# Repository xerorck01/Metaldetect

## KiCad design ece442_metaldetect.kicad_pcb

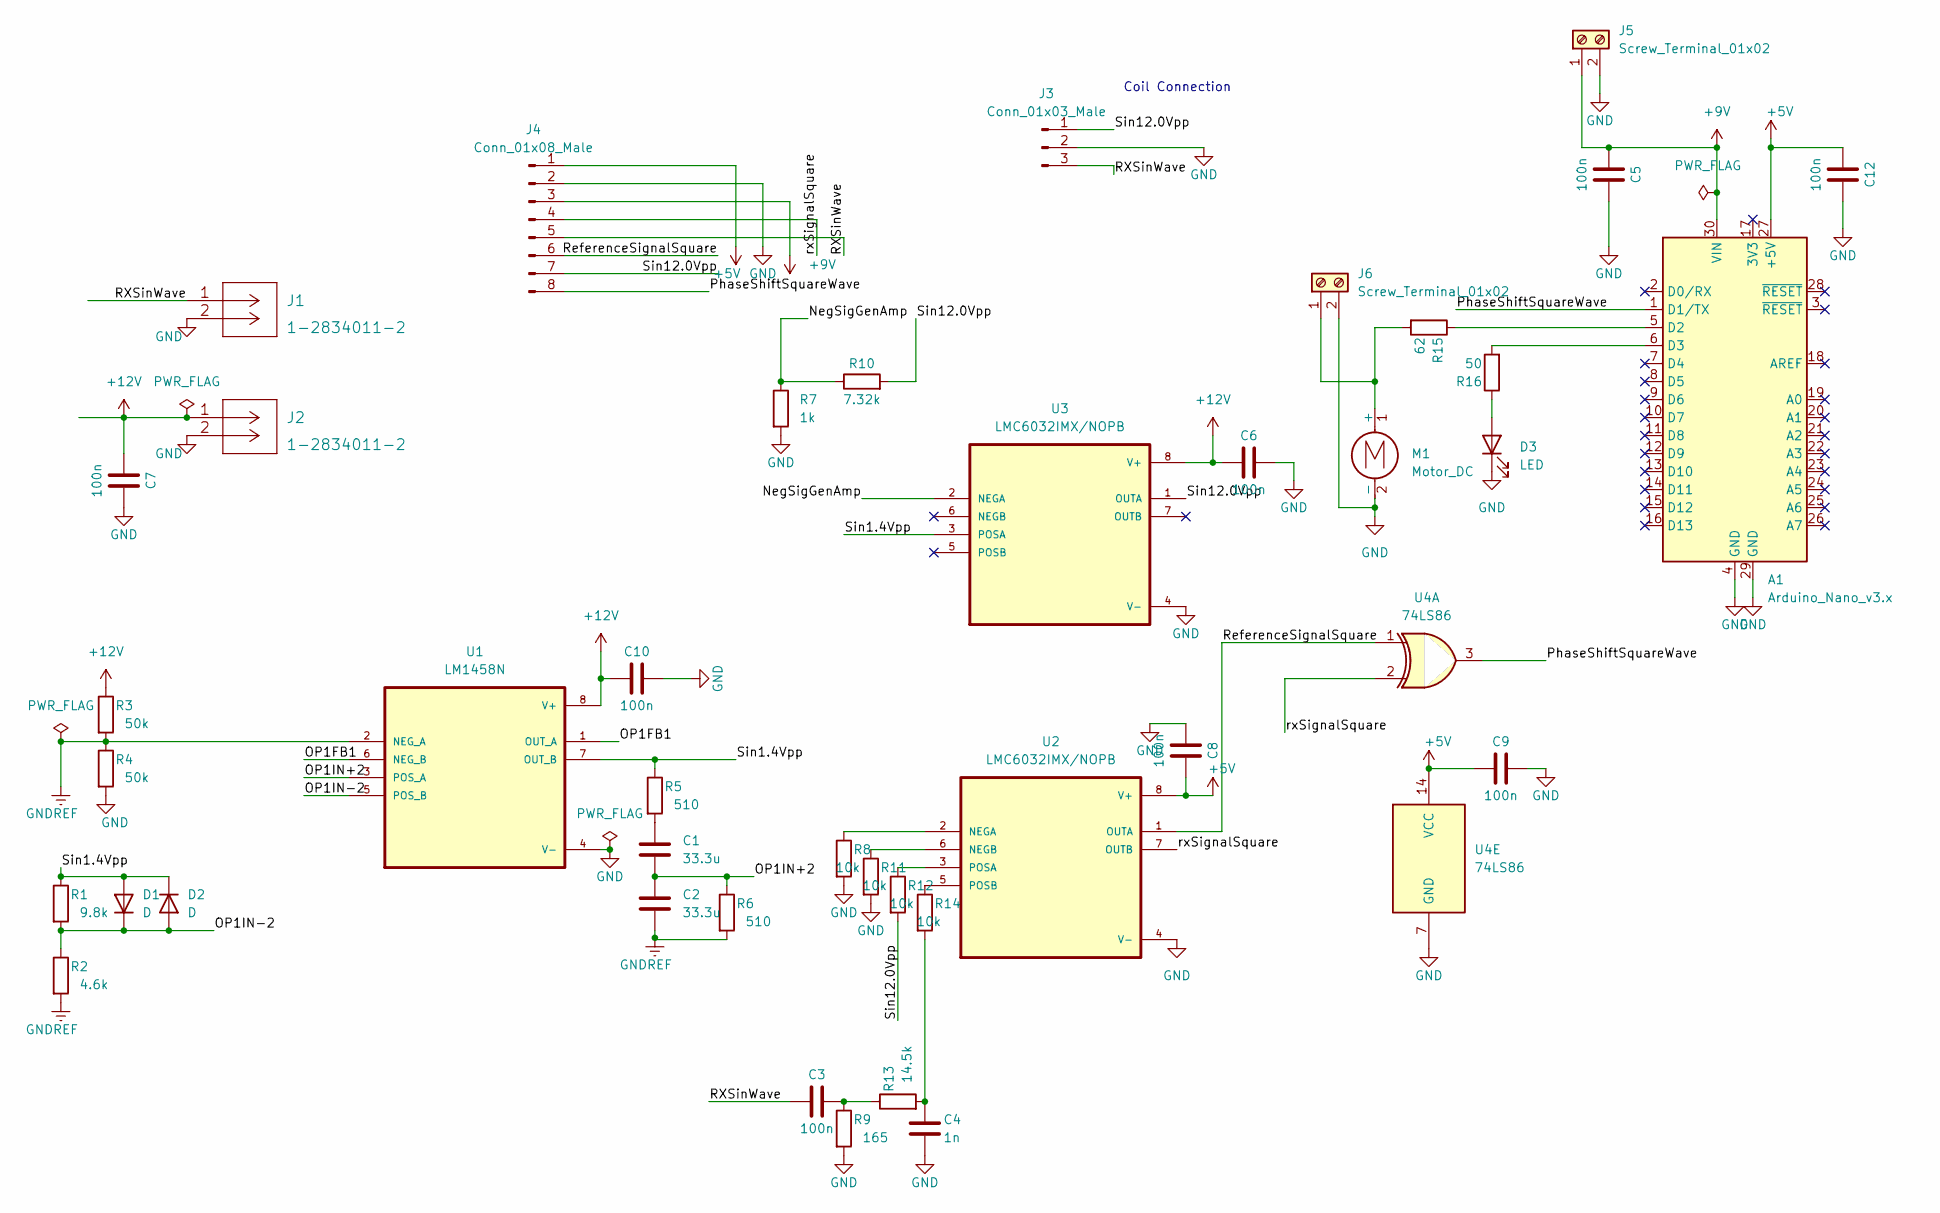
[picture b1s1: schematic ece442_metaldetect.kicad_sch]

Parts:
A1: Arduino_Nano_v3.x; Arduino_Nano
C1, C2: 33.3u; C_Rect_L7.0mm_W3.5mm_P5.00mm
C3, C5, C6, C7, C8, C9, C10, C12: 100n; C_0805_2012Metric
C4: 1n; C_0805_2012Metric
D1, D2: D; D_DO-35_SOD27_P7.62mm_Horizontal
D3: LED; LED_Rectangular_W5.0mm_H2.0mm
J1, J2: 1-2834011-2; connect_detect
J3: Conn_01x03_Male; PinHeader_1x03_P2.54mm_Horizontal
J4: Conn_01x08_Male; PinHeader_1x08_P2.54mm_Horizontal
J5, J6: Screw_Terminal_01x02; PinHeader_1x02_P2.54mm_Vertical
M1: Motor_DC; vclp_vibrator
R1: 9.8k; R_0805_2012Metric
R2: 4.6k; R_0603_1608Metric
R3, R4: 50k; R_1206_3216Metric
R5, R6: 510; R_0603_1608Metric
R7: 1k; R_1206_3216Metric
R8, R11, R12, R14: 10k; R_0805_2012Metric
R9: 165; R_1206_3216Metric
R10: 7.32k; R_0805_2012Metric
R13: 14.5k; R_0805_2012Metric
R15: 62; R_0805_2012Metric
R16: 50; R_0805_2012Metric
U1: LM1458N; DIP794-detect
U2, U3: LMC6032IMX/NOPB; SOIC127P599X175-8N
U4: 74LS86; SOIC-14_3.9x8.7mm_P1.27mm

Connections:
+5V: A1.27 (+5V), C8.2, C9.1, C12.1, J4.1, U2.8 (V+), U4.14 (VCC)
+9V: A1.30 (VIN), C5.1, J4.3, J5.1
+12V: C6.1, C7.1, C10.1, J2.1, R3.1, U1.8 (V+), U3.8 (V+)
/NegSigGenAmp: R7.1, R10.1, U3.2 (NEGA)
/OP1FB1: U1.1 (OUT_A), U1.6 (NEG_B)
/OP1IN+2: C1.2, C2.1, R6.1, U1.3 (POS_A)
/OP1IN-2: D1.1 (K), D2.2 (A), R1.2, R2.1, U1.5 (POS_B)
/PhaseShiftSquareWave: A1.1 (D1/TX), J4.8, U4.3
/RXSinWave: C3.1, J1.1, J3.3, J4.5
/ReferenceSignalSquare: J4.6, U2.1 (OUTA), U4.1
/Sin1.4Vpp: D1.2 (A), D2.1 (K), R1.1, R5.1, U1.7 (OUT_B), U3.3 (POSA)
/Sin12.0Vpp: J3.1, J4.7, R10.2, R12.2, U3.1 (OUTA)
/rxSignalSquare: J4.4, U2.7 (OUTB), U4.2
GND: A1.4 (GND), A1.29 (GND), C4.1, C5.2, C6.2, C7.2, C8.1, C9.2, C10.2, C12.2, D3.1 (K), J1.2, J2.2, J3.2, J4.2, J5.2, J6.2, M1.2 (-), R4.2, R7.2, R8.2, R9.2, R11.2, U1.4 (V-), U2.4 (V-), U3.4 (V-), U4.7 (GND)
GNDREF: C2.2, R2.2, R3.2, R4.1, R6.2, U1.2 (NEG_A)
unnamed: A1.5 (D2), R15.1
unnamed: A1.6 (D3), R16.2
unnamed: C1.1, R5.2
unnamed: C3.2, R9.1, R13.1
unnamed: C4.2, R13.2, R14.2
unnamed: D3.2 (A), R16.1
unnamed: J6.1, M1.1 (+), R15.2
unnamed: R8.1, U2.2 (NEGA)
unnamed: R11.1, U2.6 (NEGB)
unnamed: R12.1, U2.3 (POSA)
unnamed: R14.1, U2.5 (POSB)

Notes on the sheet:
Coil Connection

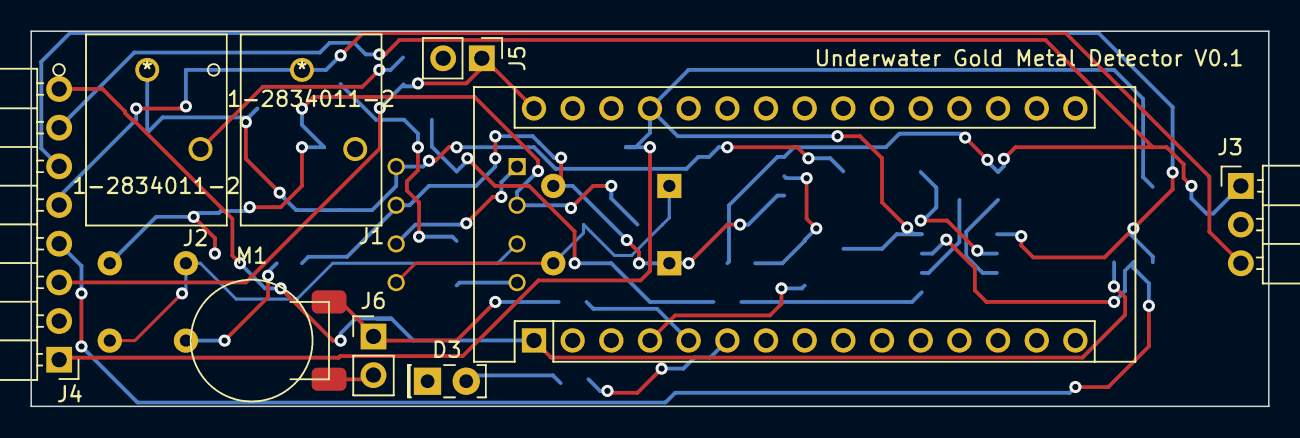
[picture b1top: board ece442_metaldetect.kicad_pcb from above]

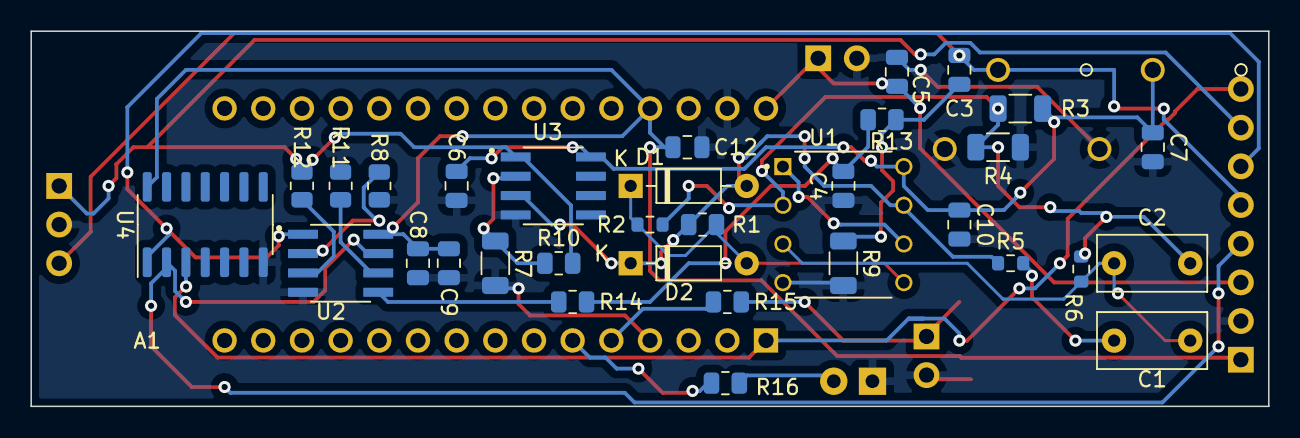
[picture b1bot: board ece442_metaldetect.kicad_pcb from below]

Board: 2 copper layers, 81.3 x 24.6 mm, 42 parts (33 on the bottom side), 26 nets.

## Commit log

2023-02-03 Add files via upload
    Version 1, need pads and pcb layout
2023-02-06 Add files via upload
    Added Coil and User Feedback modules, added BOM for respective parts
2023-02-24 added signal processing code
2023-03-13 Add files via upload
    added test points to design, critique accordingly
2023-03-17 Add files via upload
    first version pcb done, may need changes
2023-03-17 Add files via upload
    added in case i missed any of james ICs
2023-03-17 Add files via upload
    added these in case thats the issue
2023-03-17 Add files via upload
    the actual changes made
2023-03-18 updated the code so that it works
2023-03-19 moved j5 and slikscreen labels to be more clear
2023-03-19 shrunk width of board slightly, added ground pour and moved components
2023-03-19 fixed clearance violation
2023-03-19 added silkscreen text showing version
2023-04-28 Add files via upload
    Added coils enclosure solidworks file
2023-05-09 Add files via upload
    Added detector manual

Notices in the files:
parts and their libraries:
Copyright 2021 Accelerated Designs. All rights reserved.
